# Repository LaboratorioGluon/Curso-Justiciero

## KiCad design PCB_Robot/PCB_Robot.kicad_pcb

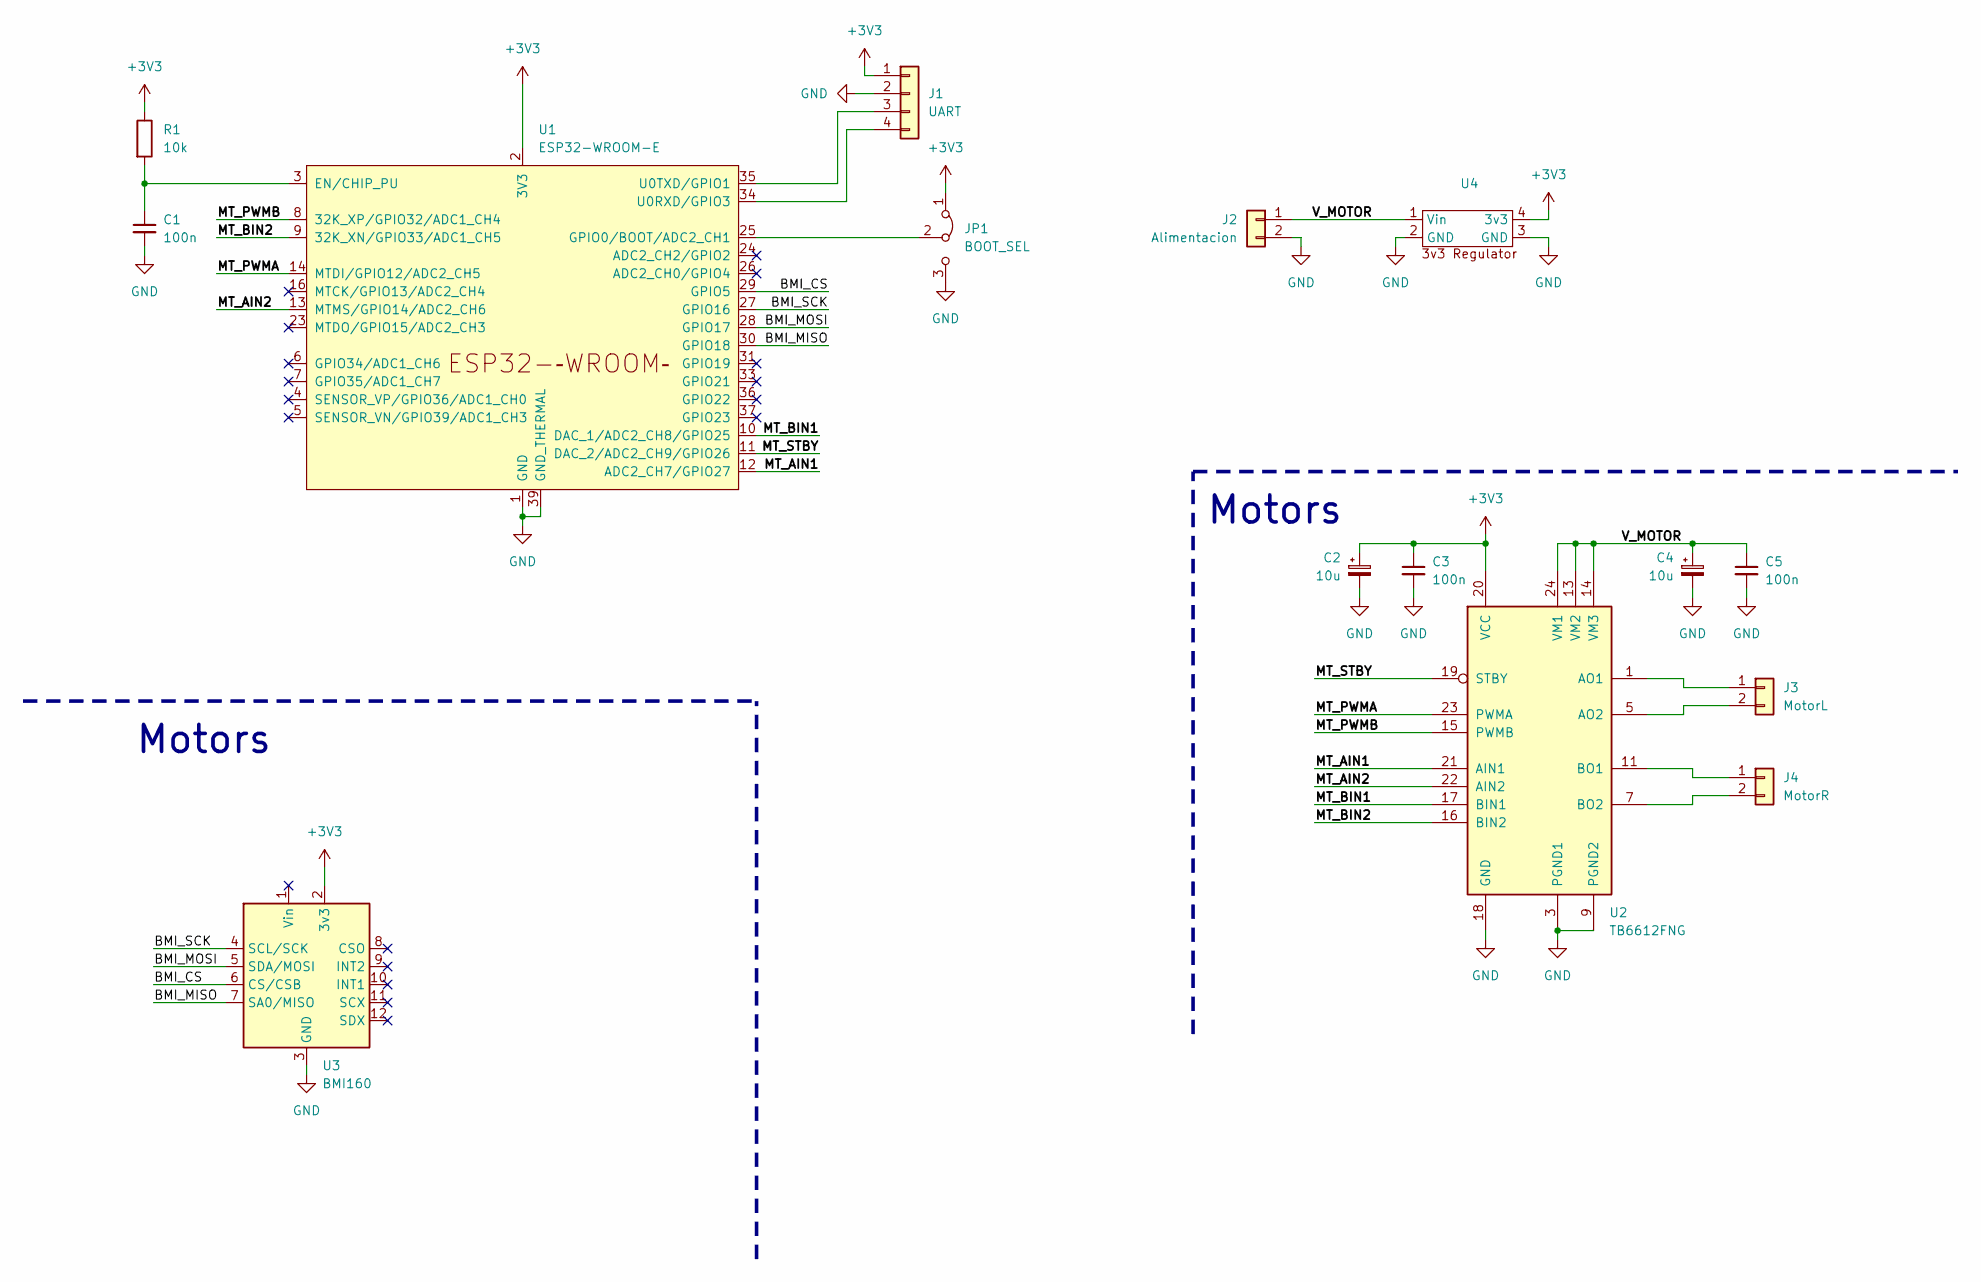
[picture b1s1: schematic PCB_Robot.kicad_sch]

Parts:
C1, C3, C5: 100n; C_0805_2012Metric_Pad1.18x1.45mm_HandSolder
C2, C4: 10u; CP_Elec_4x4.5
J1: UART; PinHeader_1x04_P2.54mm_Vertical
J2: Alimentacion; PinHeader_1x02_P2.54mm_Vertical
J3: MotorL; PinHeader_1x02_P2.54mm_Vertical
J4: MotorR; PinHeader_1x02_P2.54mm_Vertical
JP1: BOOT_SEL; PinHeader_1x03_P2.54mm_Vertical
R1: 10k; R_0805_2012Metric_Pad1.20x1.40mm_HandSolder
U1: ESP32-WROOM-E; ESP32-WROOM-32E
U2: TB6612FNG; SSOP-24_5.3x8.2mm_P0.65mm
U3: BMI160; BMI160_pinchos
U4: 3v3Reg

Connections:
+3V3: C2.1, C3.1, J1.1, JP1.1 (A), R1.1, U1.2 (3V3), U2.20 (VCC), U3.2 (3v3), U4.4 (3v3)
/BMI_CS: U1.29 (GPIO5), U3.6 (CS/CSB)
/BMI_MISO: U1.30 (GPIO18), U3.7 (SA0/MISO)
/BMI_MOSI: U1.28 (GPIO17), U3.5 (SDA/MOSI)
/BMI_SCK: U1.27 (GPIO16), U3.4 (SCL/SCK)
/MT_AIN1: U1.12 (ADC2_CH7/GPIO27), U2.21 (AIN1)
/MT_AIN2: U1.13 (MTMS/GPIO14/ADC2_CH6), U2.22 (AIN2)
/MT_BIN1: U1.10 (DAC_1/ADC2_CH8/GPIO25), U2.17 (BIN1)
/MT_BIN2: U1.9 (32K_XN/GPIO33/ADC1_CH5), U2.16 (BIN2)
/MT_PWMA: U1.14 (MTDI/GPIO12/ADC2_CH5), U2.23 (PWMA)
/MT_PWMB: U1.8 (32K_XP/GPIO32/ADC1_CH4), U2.15 (PWMB)
/MT_STBY: U1.11 (DAC_2/ADC2_CH9/GPIO26), U2.19 (STBY)
/V_MOTOR: C4.1, C5.1, J2.1, U2.13 (VM2), U2.14 (VM3), U2.24 (VM1), U4.1 (Vin)
GND: C1.2, C2.2, C3.2, C4.2, C5.2, J1.2, J2.2, JP1.3 (B), U1.1 (GND), U1.15 (GND), U1.38 (GND), U1.39 (GND_THERMAL), U2.3 (PGND1), U2.4 (PGND1), U2.9 (PGND2), U2.10 (PGND2), U2.18 (GND), U3.3 (GND), U4.2 (GND), U4.3 (GND)
unnamed: J1.3, U1.35 (U0TXD/GPIO1)
unnamed: J1.4, U1.34 (U0RXD/GPIO3)
unnamed: J3.1, U2.1 (AO1), U2.2 (AO1)
unnamed: J3.2, U2.5 (AO2), U2.6 (AO2)
unnamed: J4.1, U2.11 (BO1), U2.12 (BO1)
unnamed: J4.2, U2.7 (BO2), U2.8 (BO2)
unnamed: JP1.2 (C), U1.25 (GPIO0/BOOT/ADC2_CH1)
unnamed: C1.1, R1.2, U1.3 (EN/CHIP_PU)

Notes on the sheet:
Motors

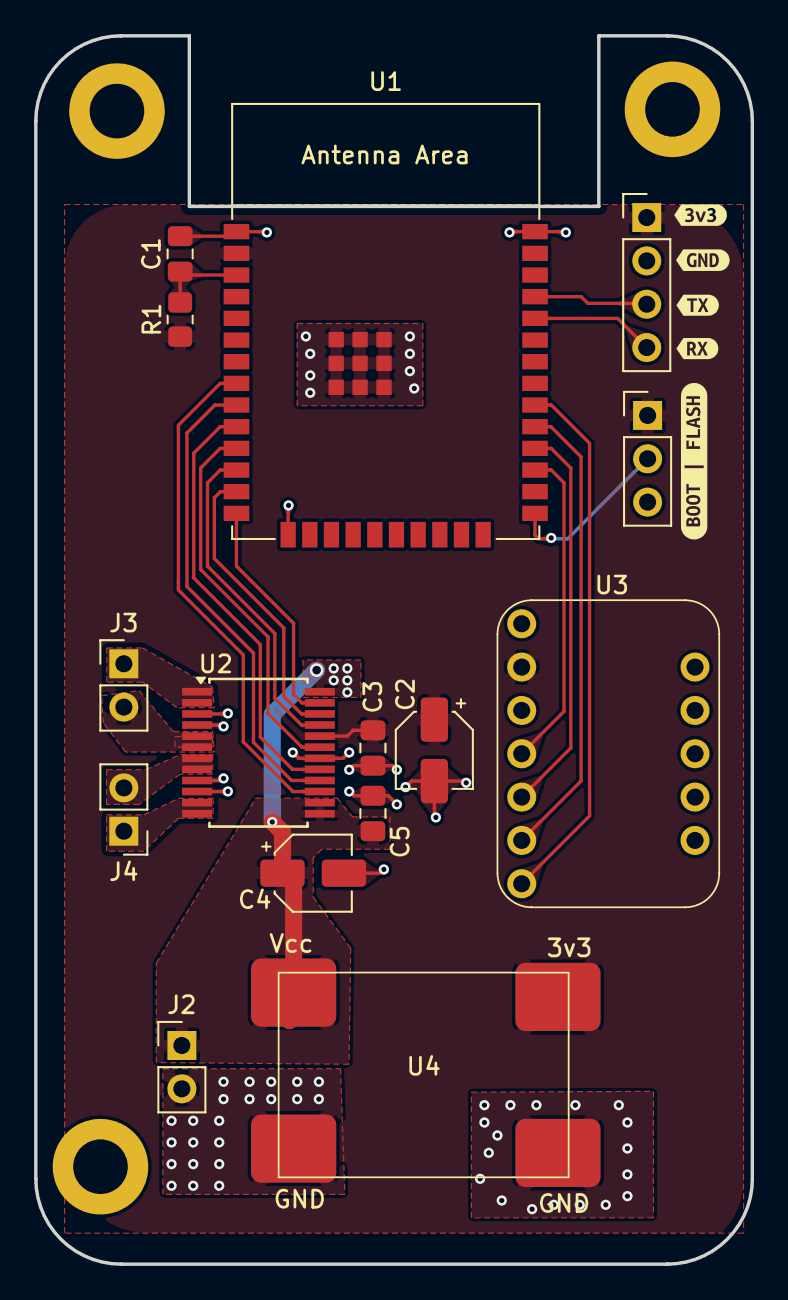
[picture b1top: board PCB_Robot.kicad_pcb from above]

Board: 2 copper layers, 42.0 x 72.0 mm, 20 parts (0 on the bottom side), 22 nets.

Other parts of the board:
kibuzzard-684B1A20: G***; kibuzzard-684B1A20
kibuzzard-684B1A93: G***; kibuzzard-684B1A93
kibuzzard-684B1AB0: G***; kibuzzard-684B1AB0
kibuzzard-684B1AB8: G***; kibuzzard-684B1AB8
kibuzzard-684B1AD4: G***; kibuzzard-684B1AD4

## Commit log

2025-01-16 First SPI transaction
2025-01-17 some refactor
2025-01-17 code fixes
2025-01-30 Bmi160 class created
2025-01-30 BMI160 with templates
2025-02-22 Motores moviendose
2025-03-06 Movimiento motores
2025-03-06 Robot equilibrado
2025-03-27 ESP-NOW working
2025-04-18 Mando, Robot y libreria
2025-05-08 Esquematico hecho en kicad
2025-06-27 Arreglado código para la el pid y el calculo del angulo
2025-07-03 Codigo final robot funcionando
2025-07-03 PCB Actualizda
